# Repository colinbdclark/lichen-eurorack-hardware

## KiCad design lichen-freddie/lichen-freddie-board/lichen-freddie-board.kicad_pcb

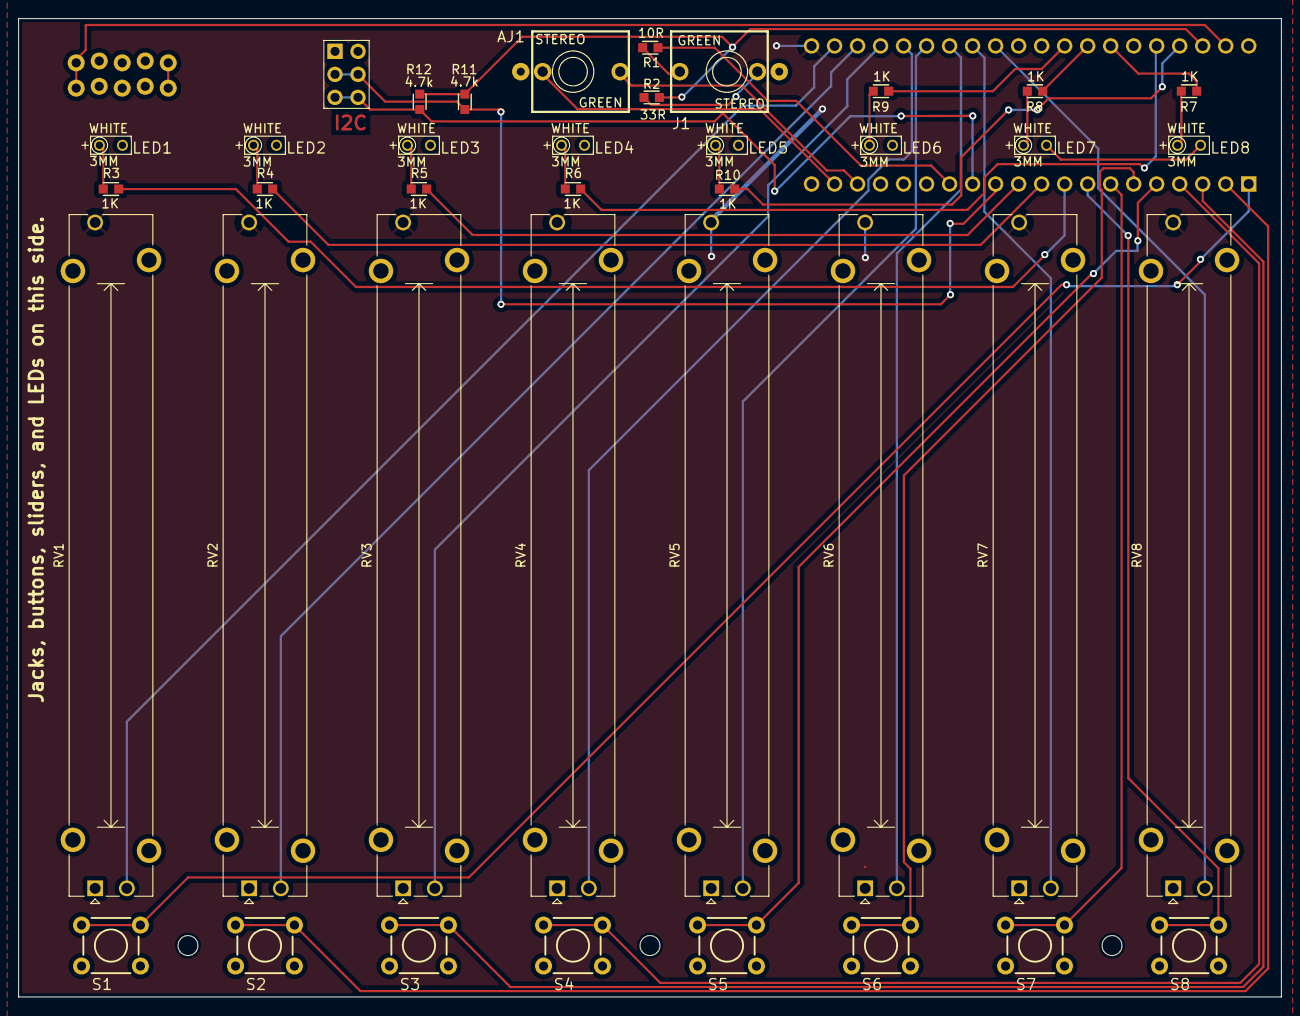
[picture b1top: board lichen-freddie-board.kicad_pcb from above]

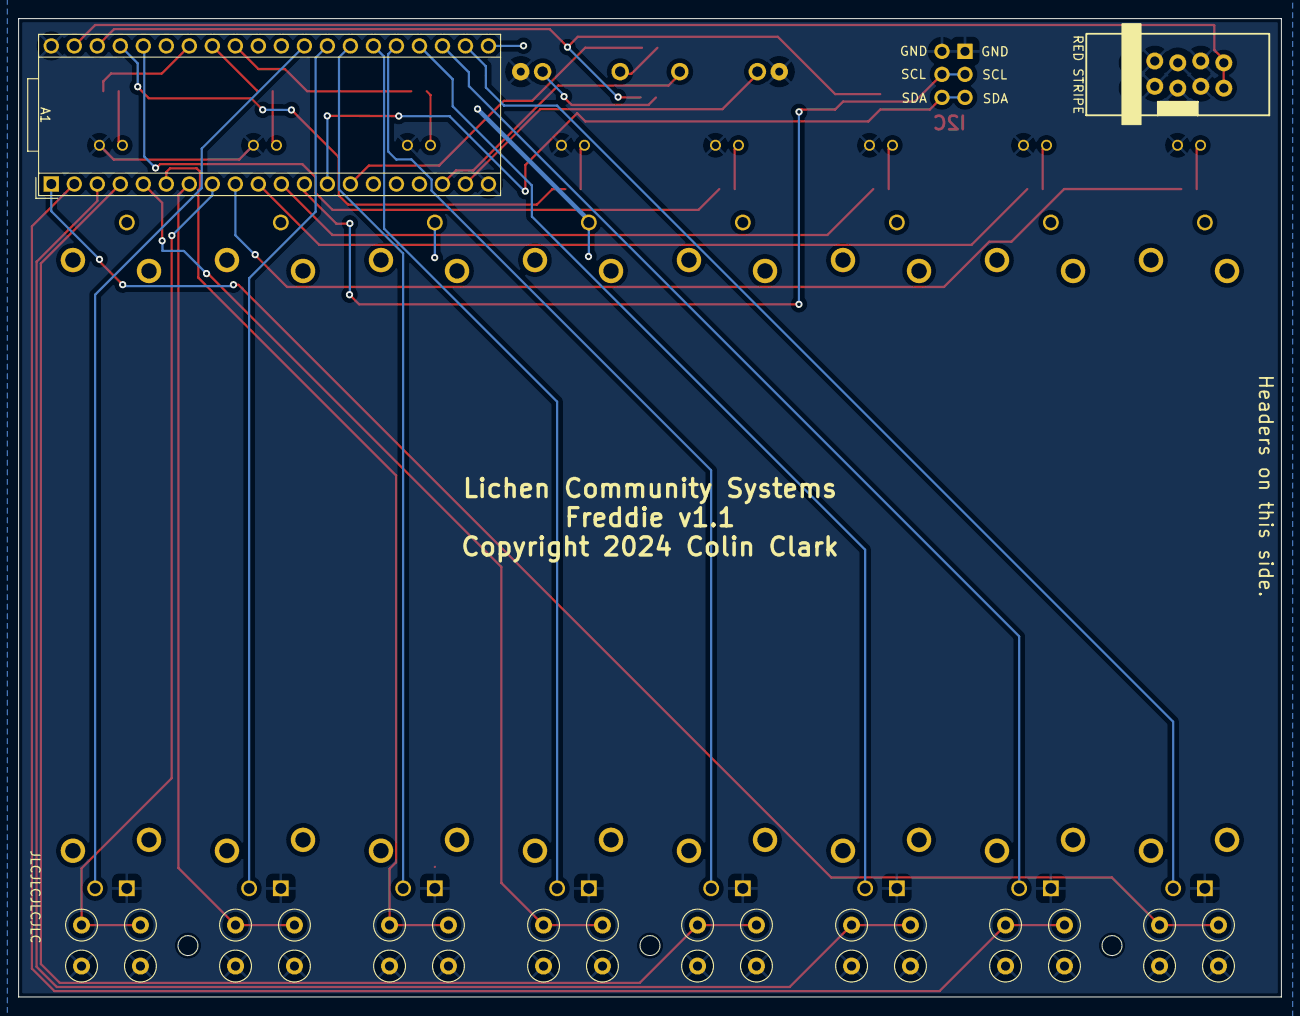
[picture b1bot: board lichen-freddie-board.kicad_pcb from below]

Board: 2 copper layers, 139.4 x 108.0 mm, 44 parts (2 on the bottom side), 43 nets.

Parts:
A1: Electrosmith_Daisy_Seed_Rev4; Electrosmith_Daisy_Seed
AJ1: 3.5mm_Stereo; EighthInch_Stereo_PJ366ST
H1: Eurorack_Power; Eurorack_Power_2x5_Shrouded_Lock
H2: Conn_02x03; Pins_2x03_2.54mm_TH
J1: 3.5mm_Stereo; EighthInch_Stereo_PJ366ST
LED1, LED2, LED3, LED4, LED5, LED6, LED7, LED8: LED
MH1, MH2, MH3: MountingHole_2.2mm_M2
R1: 10R; R_0603
R2: 33R; R_0603
R3, R4, R5, R6, R7, R8, R9, R10: 1K; R_0603
R11, R12: 4.7k; R_0603
RV1, RV2, RV3, RV4, RV5, RV6, RV7, RV8: R_Potentiometer; Potentiometer_Bourns_PTA6043_Single_Slide_Centered
S1, S2, S3, S4, S5, S6, S7, S8: TAC_SWITCH_PTH; TL1105SPF250Q_SILK

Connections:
3V3D: A1.38 (3V3_D), R2.2, R11.1, R12.2
+3.3VA: A1.21 (3V3_A), RV1.3, RV2.3, RV3.3, RV4.3, RV5.3, RV6.3, RV7.3, RV8.3
+12V: A1.39 (VIN), H1.9 (+12V), H1.10 (+12V)
BUTTON_GPIO_1: A1.1 (USB_ID), S1.1, S1.2
BUTTON_GPIO_2: A1.2 (SD_DATA_3), S2.1, S2.2
BUTTON_GPIO_3: A1.3 (SD_DATA_2), S3.1, S3.2
BUTTON_GPIO_4: A1.4 (SD_DATA_1), S4.1, S4.2
BUTTON_GPIO_5: A1.5 (SD_DATA_0), S5.1, S5.2
BUTTON_GPIO_6: A1.6 (SD_CMD), S6.1, S6.2
BUTTON_GPIO_7: A1.7 (SD_CLK), S7.1, S7.2
BUTTON_GPIO_8: A1.8 (SPI1_CS), S8.1, S8.2
GND: A1.20 (AGND), A1.40 (DGND), AJ1.2 (SHEILD), H1.3 (GND), H1.4 (GND), H1.5 (GND), H1.6 (GND), H1.7 (GND), H1.8 (GND), H2.1 (+12V), H2.2 (+12V), J1.2 (SHEILD), LED1.K (C), LED2.K (C), LED3.K (C), LED4.K (C), LED5.K (C), LED6.K (C), LED7.K (C), LED8.K (C), RV1.1, RV2.1, RV3.1, RV4.1, RV5.1, RV6.1, RV7.1, RV8.1, S1.3, S1.4, S2.3, S2.4, S3.3, S3.4, S4.3, S4.4, S5.3, S5.4, S6.3, S6.4, S7.3, S7.4, S8.3, S8.4
I2C_SCL: A1.12 (I2C1_SCL), H2.3 (GND), H2.4 (GND), R11.2
I2C_SDA: A1.13 (I2C1_SDA), H2.5 (GND), H2.6 (GND), R12.1
LED_GPIO_1: A1.9 (SPI1_SCK), R3.1
LED_GPIO_2: A1.10 (SPI1_POCI), R4.1
LED_GPIO_3: A1.11 (SPI1_PICO), R5.1
LED_GPIO_4: A1.36 (USB_D_-), R6.1
LED_GPIO_5: A1.37 (USB_D_+), R10.2
LED_GPIO_6: A1.32 (SAI2_SD_B), R9.2
LED_GPIO_7: A1.33 (SAI2_SD_A), R8.2
LED_GPIO_8: A1.34 (SAI2_FS), R7.2
unnamed: A1.22 (ADC_0), RV1.2
unnamed: A1.23 (ADC_1), RV2.2
unnamed: A1.24 (ADC_2), RV3.2
unnamed: A1.25 (ADC_3), RV4.2
unnamed: A1.26 (ADC_4), RV5.2
unnamed: A1.27 (ADC_5), RV6.2
unnamed: A1.28 (ADC_6), RV7.2
unnamed: A1.18 (AUDIO_OUT_1), AJ1.1 (SIG)
unnamed: A1.19 (AUDIO_OUT_2), AJ1.3 (SW)
unnamed: A1.29 (DAC_OUT2), RV8.2
unnamed: J1.1 (SIG), R1.1
unnamed: J1.3 (SW), R2.1
unnamed: LED1.A, R3.2
unnamed: LED2.A, R4.2
unnamed: LED3.A, R5.2
unnamed: LED4.A, R6.2
unnamed: LED5.A, R10.1
unnamed: LED6.A, R9.1
unnamed: LED7.A, R8.1
unnamed: LED8.A, R7.1
USART_TX: A1.14 (USART1_TX), R1.2

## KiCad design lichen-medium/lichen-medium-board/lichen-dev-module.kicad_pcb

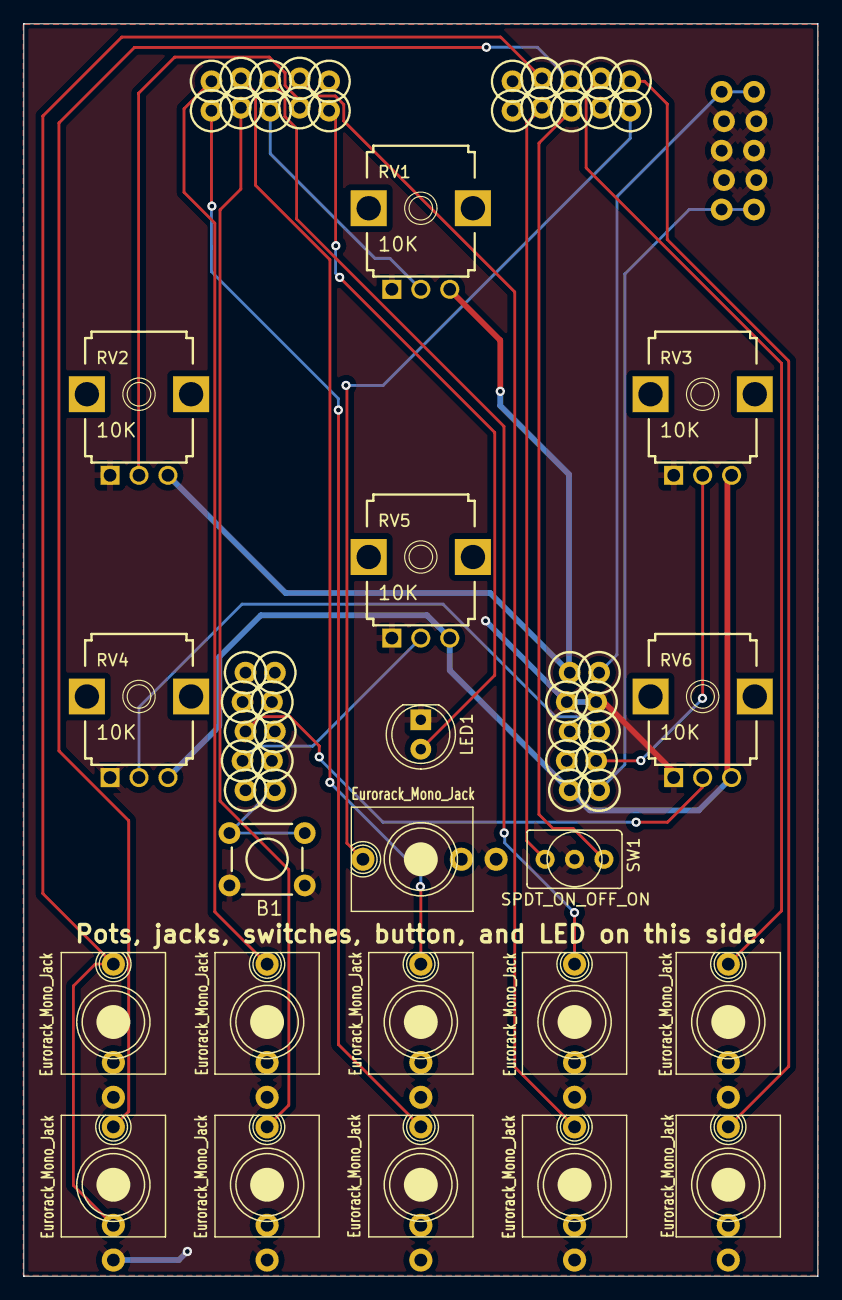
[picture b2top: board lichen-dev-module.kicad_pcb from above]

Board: 2 copper layers, 68.6 x 108.2 mm, 22 parts (1 on the bottom side), 26 nets.

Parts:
B1: TAC_SWITCH_PTH; TL1105SPF250Q_SILK
J1, J2, J3, J4, J5, J6, J7, J8, J9, J10, J11: Eurorack_Mono_Jack; AudioJack_WQP518MA
LED1: WHITE; LED_D5.0mm_Clear
MCU1: Daisy Patch Submodule; Daisy_Patch_Submodule
PWR1: Eurorack_Power; Eurorack_Power_2x5_Shrouded_Lock
RV1, RV2, RV3, RV4, RV5, RV6: 10K; 9MM_SNAP-IN_POT_SILK
SW1: SPDT_ON_OFF_ON; Switch_Toggle_SPDT_SubMini

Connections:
+3.3V: MCU1.A10 (+3V3), RV3.3, RV4.3, RV5.3, RV6.3
+5V: MCU1.A6 (+5V), RV1.3, RV2.3
+12V: MCU1.A5 (+12V), PWR1.9 (+12V), PWR1.10 (+12V)
-12V: MCU1.A1 (-12V), PWR1.1 (-12V), PWR1.2 (-12V)
AUDIO_IN_L: J7.T (Tip), J8.TN (Tip_normalize), MCU1.B4 (AUDIO_IN_L)
AUDIO_IN_R: J8.T (Tip), MCU1.B3 (AUDIO_IN_R)
AUDIO_OUT_L: J9.T (Tip), MCU1.B2 (AUDIO_OUT_L)
AUDIO_OUT_R: J10.T (Tip), MCU1.B1 (AUDIO_OUT_R)
BUTTON: B1.1, B1.2, MCU1.D1 (SPI_NSS)
CV_IN_1: J1.T (Tip), MCU1.C5 (CV1)
CV_IN_2: J2.T (Tip), MCU1.C4 (CV2)
CV_IN_3: J3.T (Tip), MCU1.C3 (CV3)
CV_IN_4: J6.T (Tip), MCU1.C2 (CV4)
CV_IN_5: J5.T (Tip), MCU1.C6 (CV5)
CV_IN_6: J4.T (Tip), MCU1.C7 (CV6)
CV_OUT_LED: LED1.2, MCU1.C10 (CV_OUT_1)
GATEIN: J11.T (Tip), MCU1.B10 (GATE_IN_1)
GND: B1.3, B1.4, J1.S (Sleeve), J2.S (Sleeve), J3.S (Sleeve), J4.S (Sleeve), J5.S (Sleeve), J6.S (Sleeve), J7.S (Sleeve), J8.S (Sleeve), J9.S (Sleeve), J10.S (Sleeve), J11.S (Sleeve), LED1.1, MCU1.A4 (GND), MCU1.A7 (GND), PWR1.3 (GND), PWR1.4 (GND), PWR1.5 (GND), PWR1.6 (GND), PWR1.7 (GND), PWR1.8 (GND), RV1.1, RV2.1, RV3.1, RV4.1, RV5.1, RV6.1, SW1.2
POT_CV_1: MCU1.C8 (CV7), RV1.2
POT_CV_2: MCU1.C9 (CV8), RV2.2
POT_CV_3: MCU1.A2 (UART_RX), RV3.2
POT_CV_4: MCU1.A3 (UART_TX), RV4.2
POT_CV_5: MCU1.D9 (SPI_MOSI), RV5.2
POT_CV_6: MCU1.D8 (SPI_MISO), RV6.2
SWITCH_ON_LEFT: MCU1.B7 (I2C1_SCL), SW1.1
SWITCH_ON_RIGHT: MCU1.B8 (I2C1_SDA), SW1.3

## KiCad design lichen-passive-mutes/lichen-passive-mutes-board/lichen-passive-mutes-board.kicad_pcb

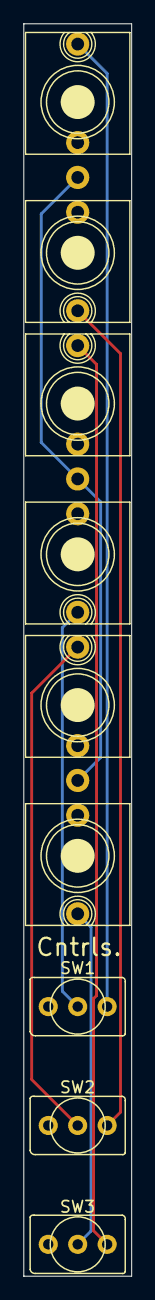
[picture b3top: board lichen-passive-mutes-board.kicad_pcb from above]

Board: 2 copper layers, 9.3 x 108.0 mm, 9 parts (0 on the bottom side), 7 nets.

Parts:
J1, J3, J5: Eurorack_Mono_Jack; AudioJack_WQP518MA
J2, J4, J6: Eurorack_Mono_Jack; AudioJack_WQP518MA_No_S
SW1, SW2, SW3: SW_SPDT; Switch_Toggle_SPDT_SubMini

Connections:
GND: J1.S (Sleeve), J3.S (Sleeve), J5.S (Sleeve)
unnamed: J1.T (Tip), SW1.1 (A)
unnamed: J2.T (Tip), SW2.1 (A)
unnamed: J3.T (Tip), SW3.1 (A)
unnamed: J4.T (Tip), SW1.2 (B)
unnamed: J5.T (Tip), SW2.2 (B)
unnamed: J6.T (Tip), SW3.2 (B)

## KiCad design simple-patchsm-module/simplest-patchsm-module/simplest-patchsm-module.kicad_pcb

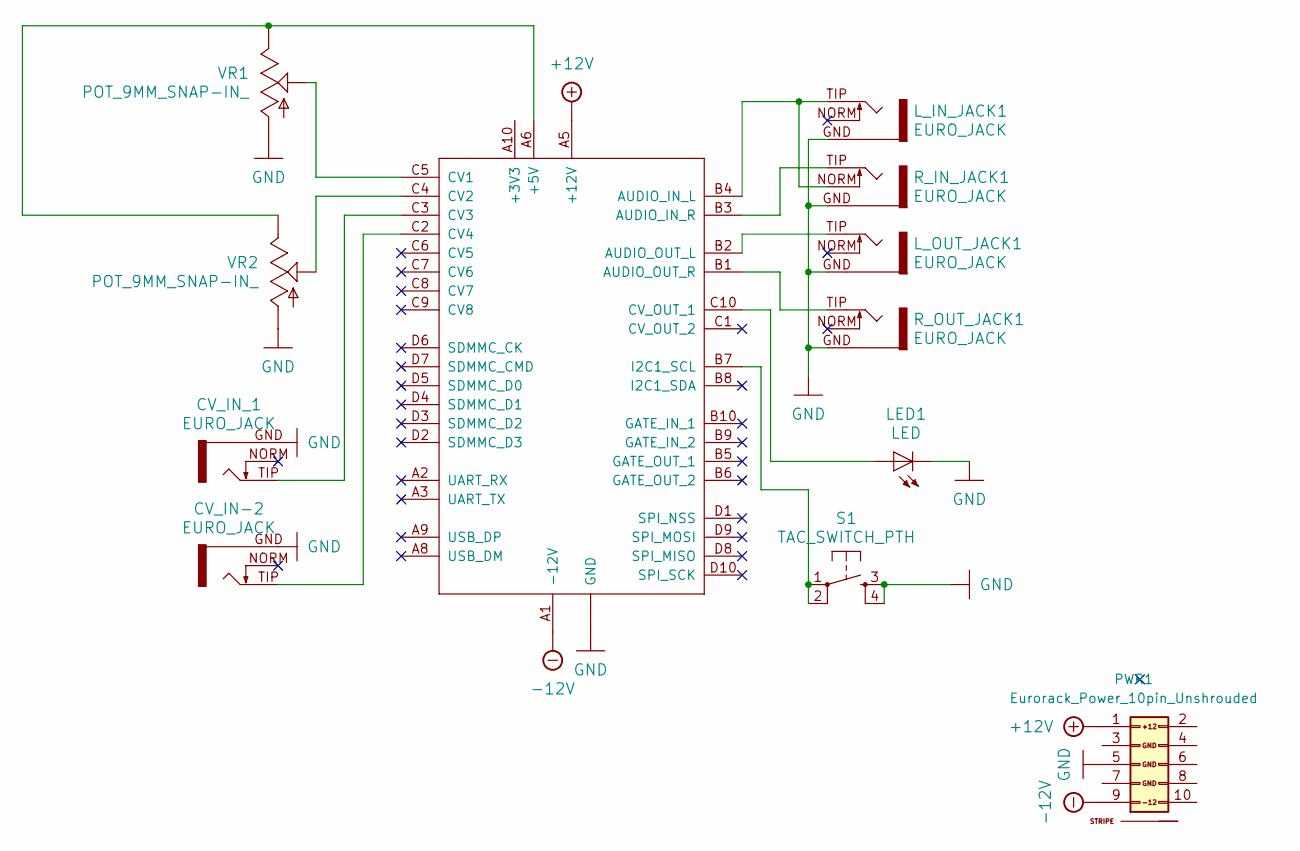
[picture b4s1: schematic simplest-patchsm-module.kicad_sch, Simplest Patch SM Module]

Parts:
CV_IN-2: EURO_JACK; S_JACK
CV_IN_1: EURO_JACK; S_JACK
LED1: LED
L_IN_JACK1: EURO_JACK; S_JACK
L_OUT_JACK1: EURO_JACK; S_JACK
PATCH_SM1: ES_DAISY_PATCH_SM_REV1
PWR1: Eurorack_Power_10pin_Unshrouded; Pins_2x05_2.54mm_TH_Europower; Part Number 1-1002FBV0T
R_IN_JACK1: EURO_JACK; S_JACK
R_OUT_JACK1: EURO_JACK; S_JACK
S1: TAC_SWITCH_PTH; TL1105SPF250Q_SILK
VR1, VR2: POT_9MM_SNAP-IN_; 9MM_SNAP-IN_POT_SILK

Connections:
+12V: PATCH_SM1.A5 (+12V), PWR1.1 (+12V)
-12V: PATCH_SM1.A1 (-12V), PWR1.9 (-12V)
GND: CV_IN-2.GND, CV_IN_1.GND, LED1.K (C), L_IN_JACK1.GND, L_OUT_JACK1.GND, PATCH_SM1.A4 (GND), PATCH_SM1.A7 (GND), PWR1.5 (GND), R_IN_JACK1.GND, R_OUT_JACK1.GND, S1.3, S1.4, VR1.1, VR2.1
unnamed: PATCH_SM1.A6 (+5V), VR1.3, VR2.3
unnamed: L_IN_JACK1.TIP, PATCH_SM1.B4 (AUDIO_IN_L), R_IN_JACK1.NORM
unnamed: PATCH_SM1.B3 (AUDIO_IN_R), R_IN_JACK1.TIP
unnamed: L_OUT_JACK1.TIP, PATCH_SM1.B2 (AUDIO_OUT_L)
unnamed: PATCH_SM1.B1 (AUDIO_OUT_R), R_OUT_JACK1.TIP
unnamed: PATCH_SM1.C5 (CV1), VR1.2
unnamed: PATCH_SM1.C4 (CV2), VR2.2
unnamed: CV_IN_1.TIP, PATCH_SM1.C3 (CV3)
unnamed: CV_IN-2.TIP, PATCH_SM1.C2 (CV4)
unnamed: LED1.A, PATCH_SM1.C10 (CV_OUT_1)
unnamed: PATCH_SM1.B7 (I2C1_SCL), S1.1, S1.2

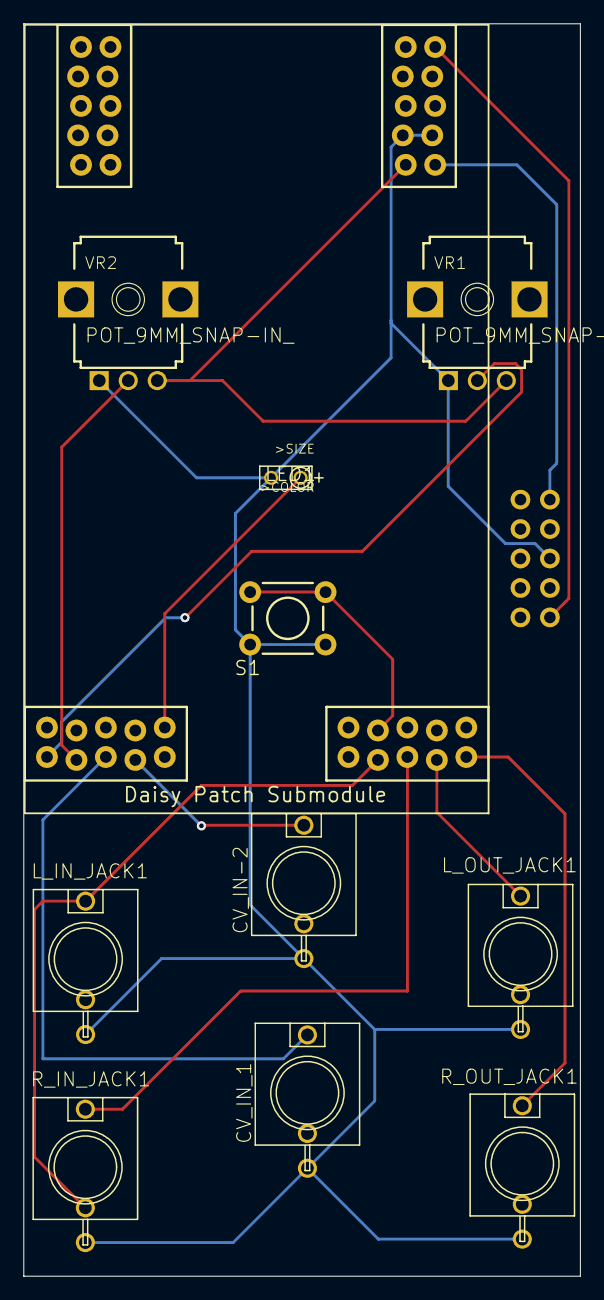
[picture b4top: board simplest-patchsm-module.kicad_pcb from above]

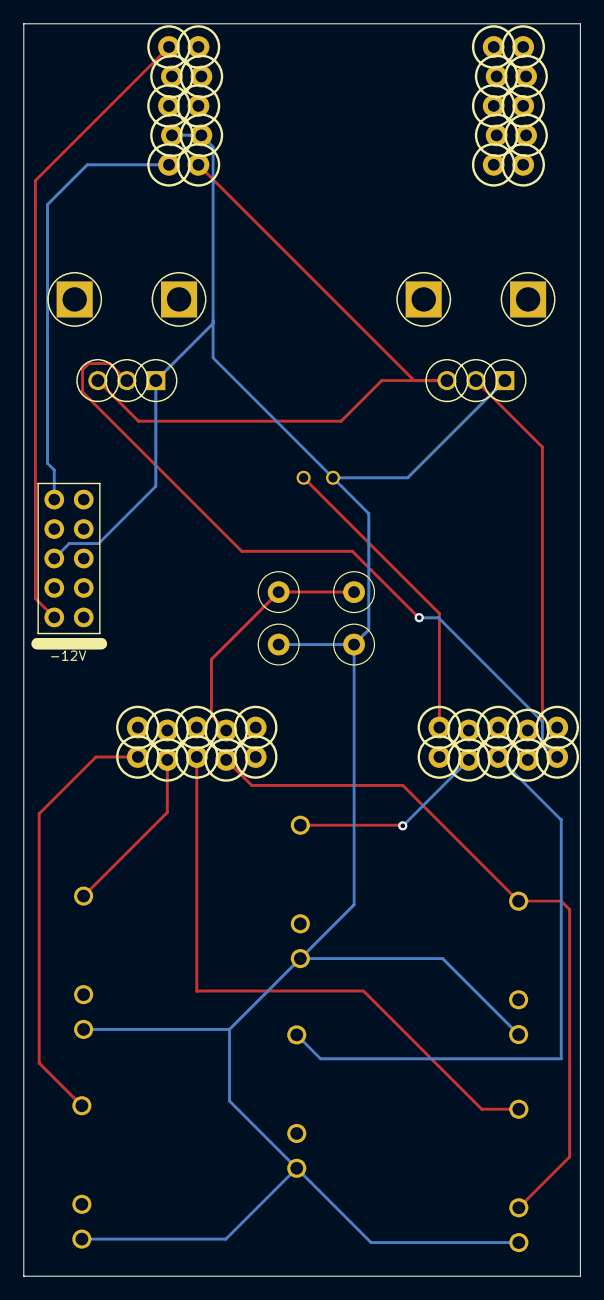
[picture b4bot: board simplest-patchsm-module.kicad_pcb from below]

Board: 2 copper layers, 48.0 x 108.0 mm, 12 parts (2 on the bottom side), 14 nets.

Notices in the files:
lichen-freddie/lichen-freddie-board/lichen-freddie-board.kicad_pcb:
Copyright 2024 Colin Clark
lichen-passive-mutes/lichen-passive-mutes-board/lichen-passive-mutes-board.kicad_pcb:
Lichen Sw v1.1, Copyright 2024 Colin Clark
